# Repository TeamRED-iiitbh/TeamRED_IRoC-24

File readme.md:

View this project on [CADLAB.io](https://cadlab.io/project/27908). 

# TeamRED_IRoC-24

```bash
git clone https://github.com/TeamRED-iiitbh/TeamRED_IRoC-24.git
git submodule update --init
```

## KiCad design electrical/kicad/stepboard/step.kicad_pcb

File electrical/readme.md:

# Hardware

## Fritzing Circuit
The Fritzing circuit `electrocal\fritzing` includes various components for prototyping and visualization, such as temperature and humidity sensors, current sensors, and IMUs, all interconnected with the Arduino Giga board.

1. Adafruit AHT20 Temperature and Humidity Sensor
2. Adafruit INA219 Current Sensor FeatherWing
3. Adafruit INA219
4. Adafruit LSM6DS33 6-DoF Accel + Gyro IMU
5. Arduino-GIGA-R1-WIFI
6. AS5600 module
7. BMI160 breakout
8. Raspberry-Pi5
9. Seeed Wio E5
10. TMC2209 Bigtree

## Ki-Cad Projects

### GIGA Board - giga.kicad_pro

- DC Motor & 2-CH Encoder - Signal Pins
    DCx_PWM, DCx_
-  TMC2209 MakerBase

- AS5600 Module

### Power Board - pdb.kicad_pro

# Firware

### Stepper Motor Control with AS5600 Encoder

system that continuously moves the motor while displaying the encoder count. The setup uses an Arduino board with the AccelStepper library for motor control and interrupt-driven encoder reading for accurate feedback
- AccelStepper.h
- AS5600.h

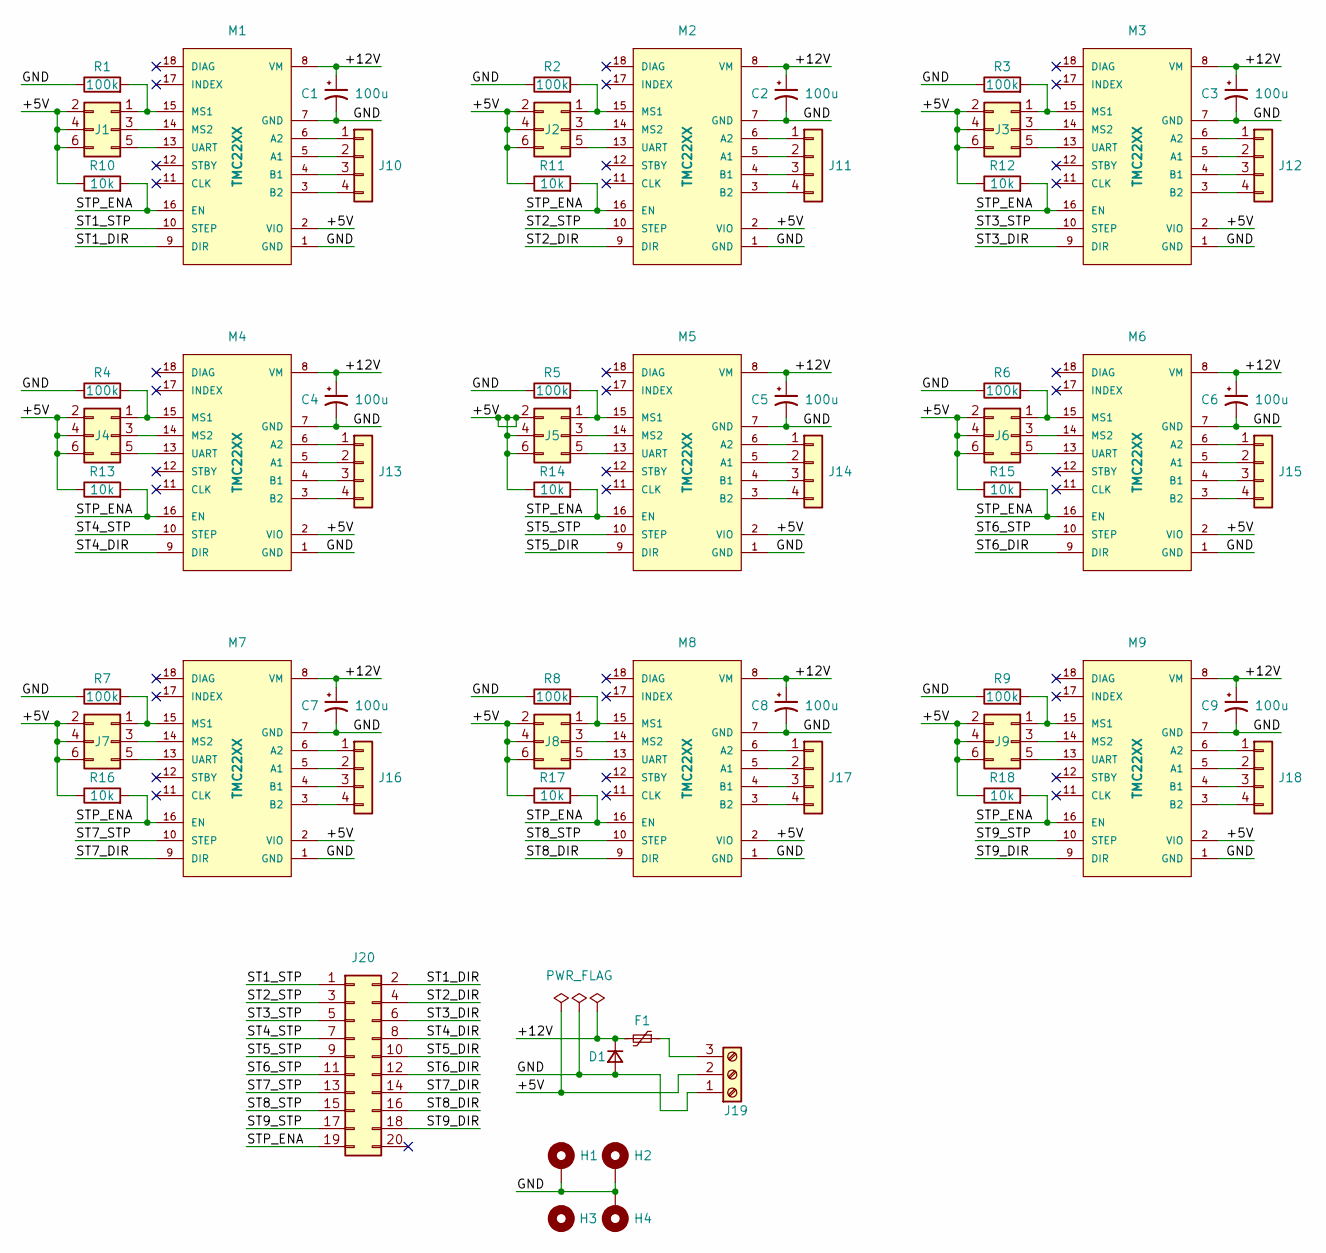
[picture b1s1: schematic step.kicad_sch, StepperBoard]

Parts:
C1, C2, C3, C4, C5, C6, C7, C8, C9: 100u; CP_Radial_D8.0mm_P2.50mm
D1: D_Small; D_DO-35_SOD27_P7.62mm_Horizontal
F1: Polyfuse_Small; Fuse_Tyco_RGEF1400
H1, H2, H4: MountingHole_Pad; MountingHole_3.2mm_M3_Pad_Via
H3: MountingHole; MountingHole_3.2mm_M3
J1, J2, J3, J4, J5, J6, J7, J8, J9: Conn_02x03_Odd_Even; PinHeader_2x03_P2.54mm_Vertical
J10, J11, J12, J13, J14, J15, J16, J17, J18: Conn_01x04; JST_XH_1x04_P2.54mm_Vertical
J19: Screw_Terminal_01x03; PhoenixContact_MSTBA_2,5_3-G-5,08_1x03_P5.08mm_Horizontal
J20: Conn_02x10_Odd_Even; PinHeader_2x10_P2.54mm_Vertical
M1, M2, M3, M4, M5, M6, M7, M8, M9: TMC22XX; MKS_TMC22XX
R1, R2, R3, R4, R5, R6, R7, R8, R9: 100k; R_Axial_DIN0204_L3.6mm_D1.6mm_P5.08mm_Horizontal
R10, R11, R12, R13, R14, R15, R16, R17, R18: 10k; R_Axial_DIN0204_L3.6mm_D1.6mm_P5.08mm_Horizontal

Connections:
/+5V: J1.2, J1.4, J1.6, J2.2, J2.4, J2.6, J3.2, J3.4, J3.6, J4.2, J4.4, J4.6, J5.2, J5.4, J5.6, J6.2, J6.4, J6.6, J7.2, J7.4, J7.6, J8.2, J8.4, J8.6, J9.2, J9.4, J9.6, J19.2, M1.2 (VIO), M2.2 (VIO), M3.2 (VIO), M4.2 (VIO), M5.2 (VIO), M6.2 (VIO), M7.2 (VIO), M8.2 (VIO), M9.2 (VIO), R10.1, R11.1, R12.1, R13.1, R14.1, R15.1, R16.1, R17.1, R18.1
/+12V: C1.1, C2.1, C3.1, C4.1, C5.1, C6.1, C7.1, C8.1, C9.1, D1.1 (K), F1.2, M1.8 (VM), M2.8 (VM), M3.8 (VM), M4.8 (VM), M5.8 (VM), M6.8 (VM), M7.8 (VM), M8.8 (VM), M9.8 (VM)
/GND: C1.2, C2.2, C3.2, C4.2, C5.2, C6.2, C7.2, C8.2, C9.2, D1.2 (A), H1.1, H2.1, H4.1, J19.1, M1.1 (GND), M1.7 (GND), M2.1 (GND), M2.7 (GND), M3.1 (GND), M3.7 (GND), M4.1 (GND), M4.7 (GND), M5.1 (GND), M5.7 (GND), M6.1 (GND), M6.7 (GND), M7.1 (GND), M7.7 (GND), M8.1 (GND), M8.7 (GND), M9.1 (GND), M9.7 (GND), R1.1, R2.1, R3.1, R4.1, R5.1, R6.1, R7.1, R8.1, R9.1
/ST1_DIR: J20.2, M1.9 (DIR)
/ST1_STP: J20.1, M1.10 (STEP)
/ST2_DIR: J20.4, M2.9 (DIR)
/ST2_STP: J20.3, M2.10 (STEP)
/ST3_DIR: J20.6, M3.9 (DIR)
/ST3_STP: J20.5, M3.10 (STEP)
/ST4_DIR: J20.8, M4.9 (DIR)
/ST4_STP: J20.7, M4.10 (STEP)
/ST5_DIR: J20.10, M5.9 (DIR)
/ST5_STP: J20.9, M5.10 (STEP)
/ST6_DIR: J20.12, M6.9 (DIR)
/ST6_STP: J20.11, M6.10 (STEP)
/ST7_DIR: J20.14, M7.9 (DIR)
/ST7_STP: J20.13, M7.10 (STEP)
/ST8_DIR: J20.16, M8.9 (DIR)
/ST8_STP: J20.15, M8.10 (STEP)
/ST9_DIR: J20.18, M9.9 (DIR)
/ST9_STP: J20.17, M9.10 (STEP)
/STP_ENA: J20.19, M1.16 (EN), M2.16 (EN), M3.16 (EN), M4.16 (EN), M5.16 (EN), M6.16 (EN), M7.16 (EN), M8.16 (EN), M9.16 (EN), R10.2, R11.2, R12.2, R13.2, R14.2, R15.2, R16.2, R17.2, R18.2
unnamed: J1.1, M1.15 (MS1), R1.2
unnamed: J1.3, M1.14 (MS2)
unnamed: J1.5, M1.13 (UART)
unnamed: J2.1, M2.15 (MS1), R2.2
unnamed: J2.3, M2.14 (MS2)
unnamed: J2.5, M2.13 (UART)
unnamed: J3.1, M3.15 (MS1), R3.2
unnamed: J3.3, M3.14 (MS2)
unnamed: J3.5, M3.13 (UART)
unnamed: J4.1, M4.15 (MS1), R4.2
unnamed: J4.3, M4.14 (MS2)
unnamed: J4.5, M4.13 (UART)
unnamed: J5.1, M5.15 (MS1), R5.2
unnamed: J5.3, M5.14 (MS2)
unnamed: J5.5, M5.13 (UART)
unnamed: J6.1, M6.15 (MS1), R6.2
unnamed: J6.3, M6.14 (MS2)
unnamed: J6.5, M6.13 (UART)
unnamed: J7.1, M7.15 (MS1), R7.2
unnamed: J7.3, M7.14 (MS2)
unnamed: J7.5, M7.13 (UART)
unnamed: J8.1, M8.15 (MS1), R8.2
unnamed: J8.3, M8.14 (MS2)
unnamed: J8.5, M8.13 (UART)
unnamed: J9.1, M9.15 (MS1), R9.2
unnamed: J9.3, M9.14 (MS2)
unnamed: J9.5, M9.13 (UART)
unnamed: J10.1, M1.6 (A2)
unnamed: J10.2, M1.5 (A1)
unnamed: J10.3, M1.4 (B1)
unnamed: J10.4, M1.3 (B2)
unnamed: J11.1, M2.6 (A2)
unnamed: J11.2, M2.5 (A1)
unnamed: J11.3, M2.4 (B1)
unnamed: J11.4, M2.3 (B2)
unnamed: J12.1, M3.6 (A2)
unnamed: J12.2, M3.5 (A1)
unnamed: J12.3, M3.4 (B1)
unnamed: J12.4, M3.3 (B2)
unnamed: J13.1, M4.6 (A2)
unnamed: J13.2, M4.5 (A1)
unnamed: J13.3, M4.4 (B1)
unnamed: J13.4, M4.3 (B2)
unnamed: J14.1, M5.6 (A2)
unnamed: J14.2, M5.5 (A1)
unnamed: J14.3, M5.4 (B1)
unnamed: J14.4, M5.3 (B2)
unnamed: J15.1, M6.6 (A2)
unnamed: J15.2, M6.5 (A1)
unnamed: J15.3, M6.4 (B1)
unnamed: J15.4, M6.3 (B2)
unnamed: J16.1, M7.6 (A2)
unnamed: J16.2, M7.5 (A1)
unnamed: J16.3, M7.4 (B1)
unnamed: J16.4, M7.3 (B2)
unnamed: J17.1, M8.6 (A2)
unnamed: J17.2, M8.5 (A1)
unnamed: J17.3, M8.4 (B1)
unnamed: J17.4, M8.3 (B2)
unnamed: J18.1, M9.6 (A2)
unnamed: J18.2, M9.5 (A1)
unnamed: J18.3, M9.4 (B1)
unnamed: J18.4, M9.3 (B2)
unnamed: F1.1, J19.3

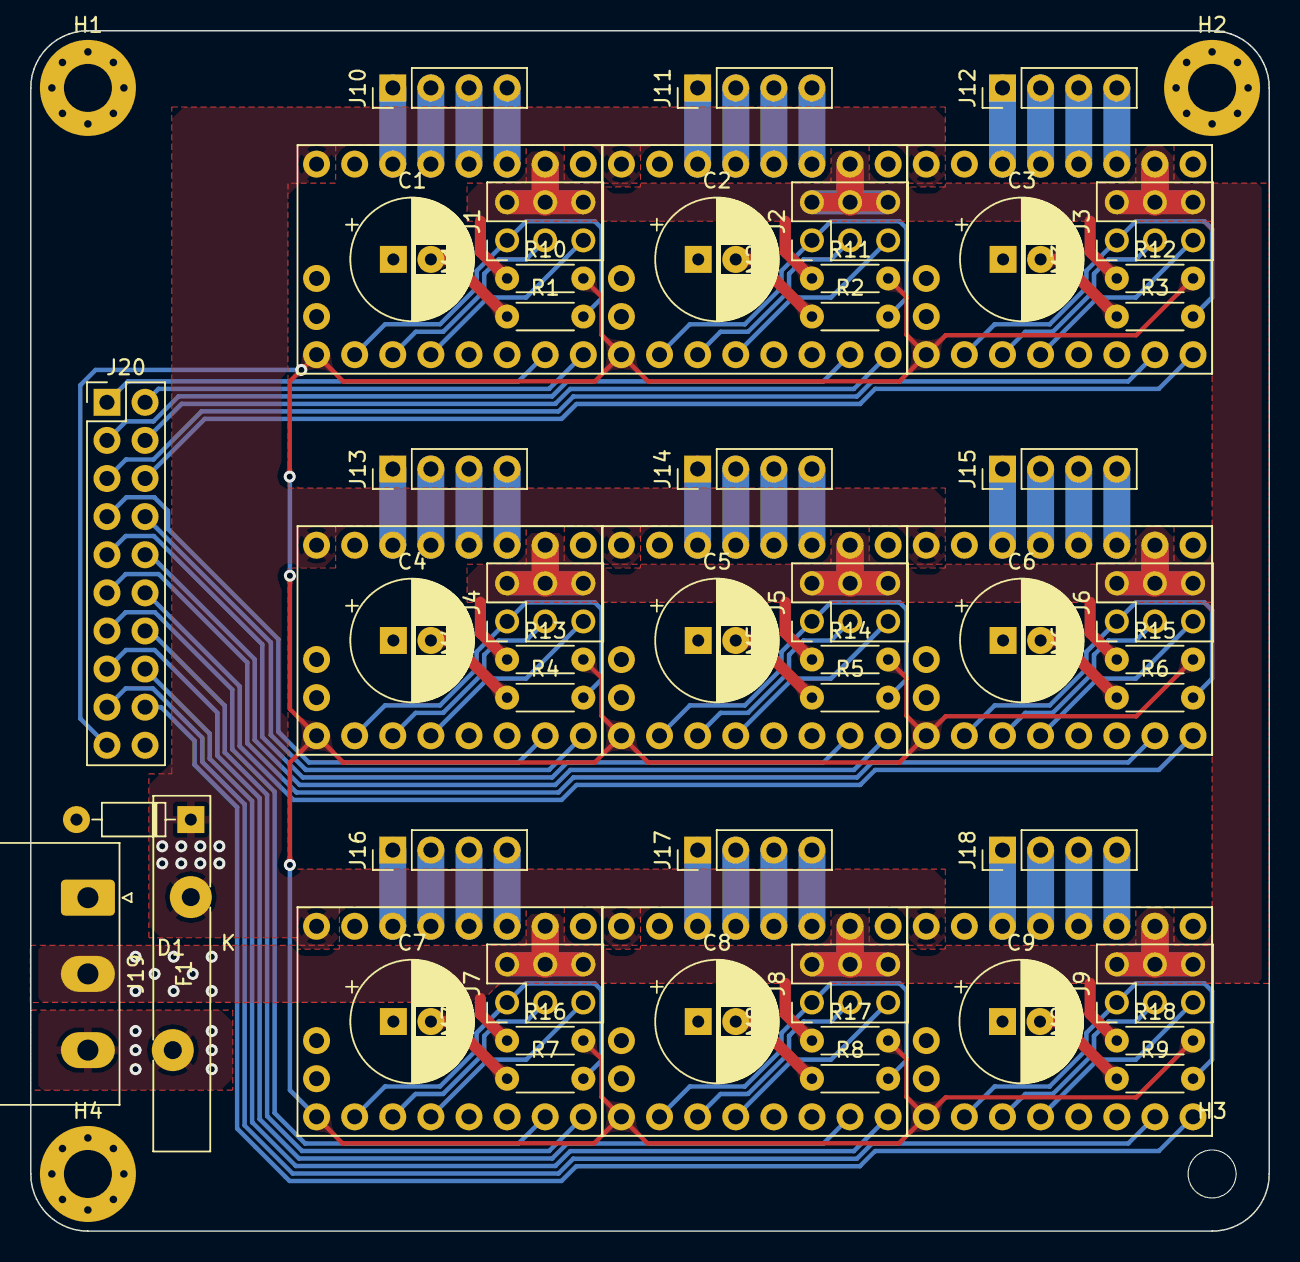
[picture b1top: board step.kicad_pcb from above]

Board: 2 copper layers, 82.6 x 80.0 mm, 62 parts (0 on the bottom side), 86 nets.

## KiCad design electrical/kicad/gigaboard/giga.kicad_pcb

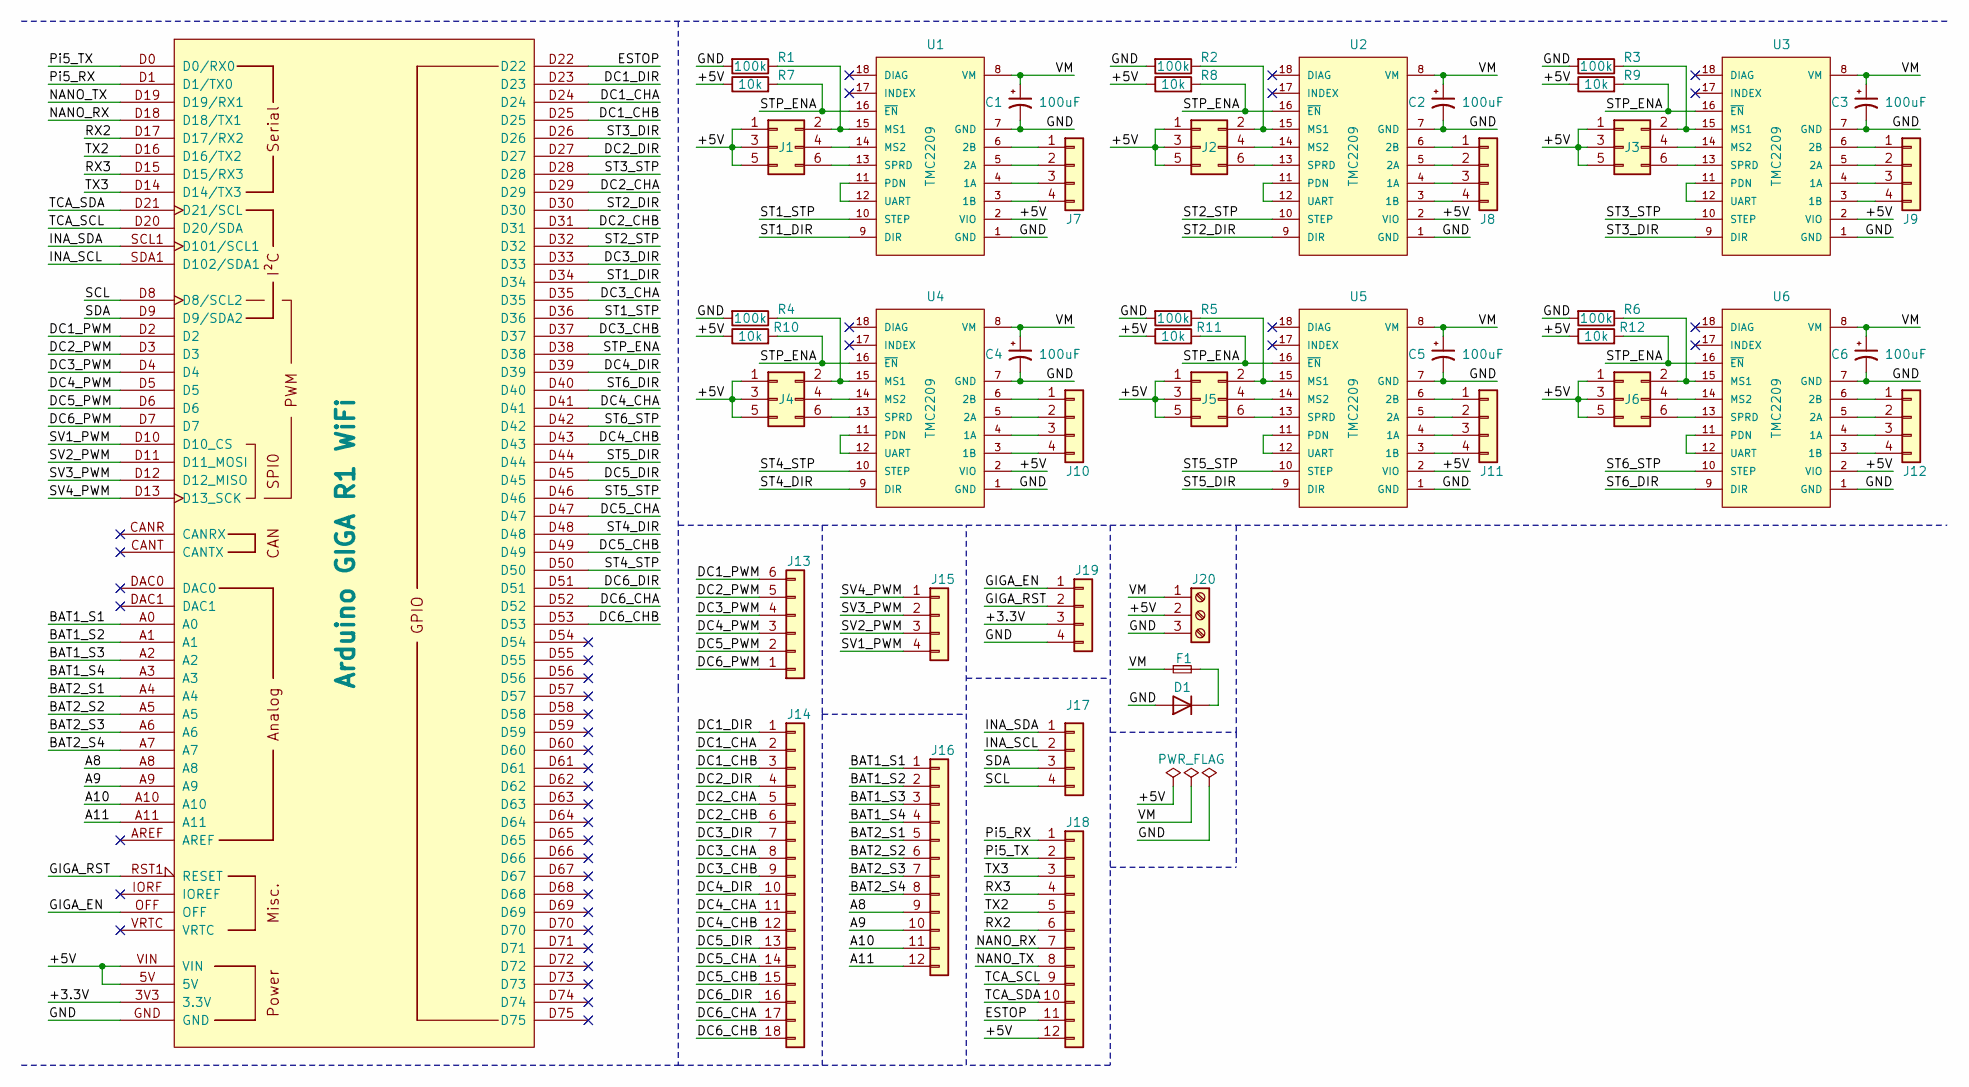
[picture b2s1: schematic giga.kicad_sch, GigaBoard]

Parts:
A1: Arduino GIGA R1 WiFi; Arduino_Giga-R1
C1, C2, C3, C4, C5, C6: 100uF; CP_Elec_6.3x7.7
D1: D; D_DO-35_SOD27_P7.62mm_Horizontal
F1: F_Small; Fuseholder_Blade_Mini_Keystone_3568
J1: Conn_02x03_Counter_Clockwise; PinHeader_2x03_P2.54mm_Vertical
J2, J3, J4, J5, J6: Conn_02x04_Counter_Clockwise; PinHeader_2x03_P2.54mm_Vertical
J7, J8, J9, J10, J11, J12, J15, J17, J19: Conn_01x04; PinHeader_1x04_P2.54mm_Vertical
J13: Conn_01x06; PinHeader_1x06_P2.54mm_Vertical
J14: Conn_01x18; PinHeader_1x18_P2.54mm_Vertical
J16, J18: Conn_01x12; PinHeader_1x12_P2.54mm_Vertical
J20: Screw_Terminal_01x03; PhoenixContact_MSTBA_2,5_3-G-5,08_1x03_P5.08mm_Horizontal
R1, R2, R3, R4, R5, R6: 100k; R_1206_3216Metric_Pad1.30x1.75mm_HandSolder
R7, R8, R9, R10, R11, R12: 10k; R_1206_3216Metric_Pad1.30x1.75mm_HandSolder
U1, U2, U3, U4, U5, U6: TMC2209; MKS_TMC2209

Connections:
/+3.3V: A1.3V3 (3.3V), J19.3
/+5V: A1.5V, A1.VIN, J1.1, J1.3, J1.5, J2.1, J2.3, J2.5, J3.1, J3.3, J3.5, J4.1, J4.3, J4.5, J5.1, J5.3, J5.5, J6.1, J6.3, J6.5, J18.12, J20.2, R7.1, R8.1, R9.1, R10.1, R11.1, R12.1, U1.2 (VIO), U2.2 (VIO), U3.2 (VIO), U4.2 (VIO), U5.2 (VIO), U6.2 (VIO)
/A8: A1.A8, J16.9
/A9: A1.A9, J16.10
/A10: A1.A10, J16.11
/A11: A1.A11, J16.12
/BAT1_S1: A1.A0, J16.1
/BAT1_S2: A1.A1, J16.2
/BAT1_S3: A1.A2, J16.3
/BAT1_S4: A1.A3, J16.4
/BAT2_S1: A1.A4, J16.5
/BAT2_S2: A1.A5, J16.6
/BAT2_S3: A1.A6, J16.7
/BAT2_S4: A1.A7, J16.8
/DC1_CHA: A1.D24, J14.2
/DC1_CHB: A1.D25, J14.3
/DC1_DIR: A1.D23, J14.1
/DC1_PWM: A1.D2, J13.6
/DC2_CHA: A1.D29, J14.5
/DC2_CHB: A1.D31, J14.6
/DC2_DIR: A1.D27, J14.4
/DC2_PWM: A1.D3, J13.5
/DC3_CHA: A1.D35, J14.8
/DC3_CHB: A1.D37, J14.9
/DC3_DIR: A1.D33, J14.7
/DC3_PWM: A1.D4, J13.4
/DC4_CHA: A1.D41, J14.11
/DC4_CHB: A1.D43, J14.12
/DC4_DIR: A1.D39, J14.10
/DC4_PWM: A1.D5, J13.3
/DC5_CHA: A1.D47, J14.14
/DC5_CHB: A1.D49, J14.15
/DC5_DIR: A1.D45, J14.13
/DC5_PWM: A1.D6, J13.2
/DC6_CHA: A1.D52, J14.17
/DC6_CHB: A1.D53, J14.18
/DC6_DIR: A1.D51, J14.16
/DC6_PWM: A1.D7, J13.1
/ESTOP: A1.D22, J18.11
/GIGA_EN: A1.OFF, J19.1
/GIGA_RST: A1.RST1 (RESET), J19.2
/GND: A1.GND, C1.2, C2.2, C3.2, C4.2, C5.2, C6.2, D1.2 (A), J19.4, J20.3, R1.2, R2.2, R3.2, R4.2, R5.2, R6.2, U1.1 (GND), U1.7 (GND), U2.1 (GND), U2.7 (GND), U3.1 (GND), U3.7 (GND), U4.1 (GND), U4.7 (GND), U5.1 (GND), U5.7 (GND), U6.1 (GND), U6.7 (GND)
/INA_SCL: A1.SDA1 (D102/SDA1), J17.2
/INA_SDA: A1.SCL1 (D101/SCL1), J17.1
/NANO_RX: A1.D18 (D18/TX1), J18.7
/NANO_TX: A1.D19 (D19/RX1), J18.8
/Pi5_RX: A1.D1 (D1/TX0), J18.1
/Pi5_TX: A1.D0 (D0/RX0), J18.2
/RX2: A1.D17 (D17/RX2), J18.6
/RX3: A1.D15 (D15/RX3), J18.4
/SCL: A1.D8 (D8/SCL2), J17.4
/SDA: A1.D9 (D9/SDA2), J17.3
/ST1_DIR: A1.D34, U1.9 (DIR)
/ST1_STP: A1.D36, U1.10 (STEP)
/ST2_DIR: A1.D30, U2.9 (DIR)
/ST2_STP: A1.D32, U2.10 (STEP)
/ST3_DIR: A1.D26, U3.9 (DIR)
/ST3_STP: A1.D28, U3.10 (STEP)
/ST4_DIR: A1.D48, U4.9 (DIR)
/ST4_STP: A1.D50, U4.10 (STEP)
/ST5_DIR: A1.D44, U5.9 (DIR)
/ST5_STP: A1.D46, U5.10 (STEP)
/ST6_DIR: A1.D40, U6.9 (DIR)
/ST6_STP: A1.D42, U6.10 (STEP)
/STP_ENA: A1.D38, R7.2, R8.2, R9.2, R10.2, R11.2, R12.2, U1.16 (~EN), U2.16 (~EN), U3.16 (~EN), U4.16 (~EN), U5.16 (~EN), U6.16 (~EN)
/SV1_PWM: A1.D10 (D10_CS), J15.4
/SV2_PWM: A1.D11 (D11_MOSI), J15.3
/SV3_PWM: A1.D12 (D12_MISO), J15.2
/SV4_PWM: A1.D13 (D13_SCK), J15.1
/TCA_SCL: A1.D20 (D20/SDA), J18.9
/TCA_SDA: A1.D21 (D21/SCL), J18.10
/TX2: A1.D16 (D16/TX2), J18.5
/TX3: A1.D14 (D14/TX3), J18.3
/VM: C1.1, C2.1, C3.1, C4.1, C5.1, C6.1, F1.1, J20.1, U1.8 (VM), U2.8 (VM), U3.8 (VM), U4.8 (VM), U5.8 (VM), U6.8 (VM)
unnamed: D1.1 (K), F1.2
unnamed: J1.2, R1.1, U1.15 (MS1)
unnamed: J1.4, U1.14 (MS2)
unnamed: J1.6, U1.13 (SPRD)
unnamed: J2.2, R2.1, U2.15 (MS1)
unnamed: J2.4, U2.14 (MS2)
unnamed: J2.6, U2.13 (SPRD)
unnamed: J3.2, R3.1, U3.15 (MS1)
unnamed: J3.4, U3.14 (MS2)
unnamed: J3.6, U3.13 (SPRD)
unnamed: J4.2, R4.1, U4.15 (MS1)
unnamed: J4.4, U4.14 (MS2)
unnamed: J4.6, U4.13 (SPRD)
unnamed: J5.2, R5.1, U5.15 (MS1)
unnamed: J5.4, U5.14 (MS2)
unnamed: J5.6, U5.13 (SPRD)
unnamed: J6.2, R6.1, U6.15 (MS1)
unnamed: J6.4, U6.14 (MS2)
unnamed: J6.6, U6.13 (SPRD)
unnamed: J7.1, U1.6 (2B)
unnamed: J7.2, U1.5 (2A)
unnamed: J7.3, U1.4 (1A)
unnamed: J7.4, U1.3 (1B)
unnamed: J8.1, U2.6 (2B)
unnamed: J8.2, U2.5 (2A)
unnamed: J8.3, U2.4 (1A)
unnamed: J8.4, U2.3 (1B)
unnamed: J9.1, U3.6 (2B)
unnamed: J9.2, U3.5 (2A)
unnamed: J9.3, U3.4 (1A)
unnamed: J9.4, U3.3 (1B)
unnamed: J10.1, U4.6 (2B)
unnamed: J10.2, U4.5 (2A)
unnamed: J10.3, U4.4 (1A)
unnamed: J10.4, U4.3 (1B)
unnamed: J11.1, U5.6 (2B)
unnamed: J11.2, U5.5 (2A)
unnamed: J11.3, U5.4 (1A)
unnamed: J11.4, U5.3 (1B)
unnamed: J12.1, U6.6 (2B)
unnamed: J12.2, U6.5 (2A)
unnamed: J12.3, U6.4 (1A)
unnamed: J12.4, U6.3 (1B)
unnamed: U1.11 (PDN), U1.12 (UART)
unnamed: U2.11 (PDN), U2.12 (UART)
unnamed: U3.11 (PDN), U3.12 (UART)
unnamed: U4.11 (PDN), U4.12 (UART)
unnamed: U5.11 (PDN), U5.12 (UART)
unnamed: U6.11 (PDN), U6.12 (UART)

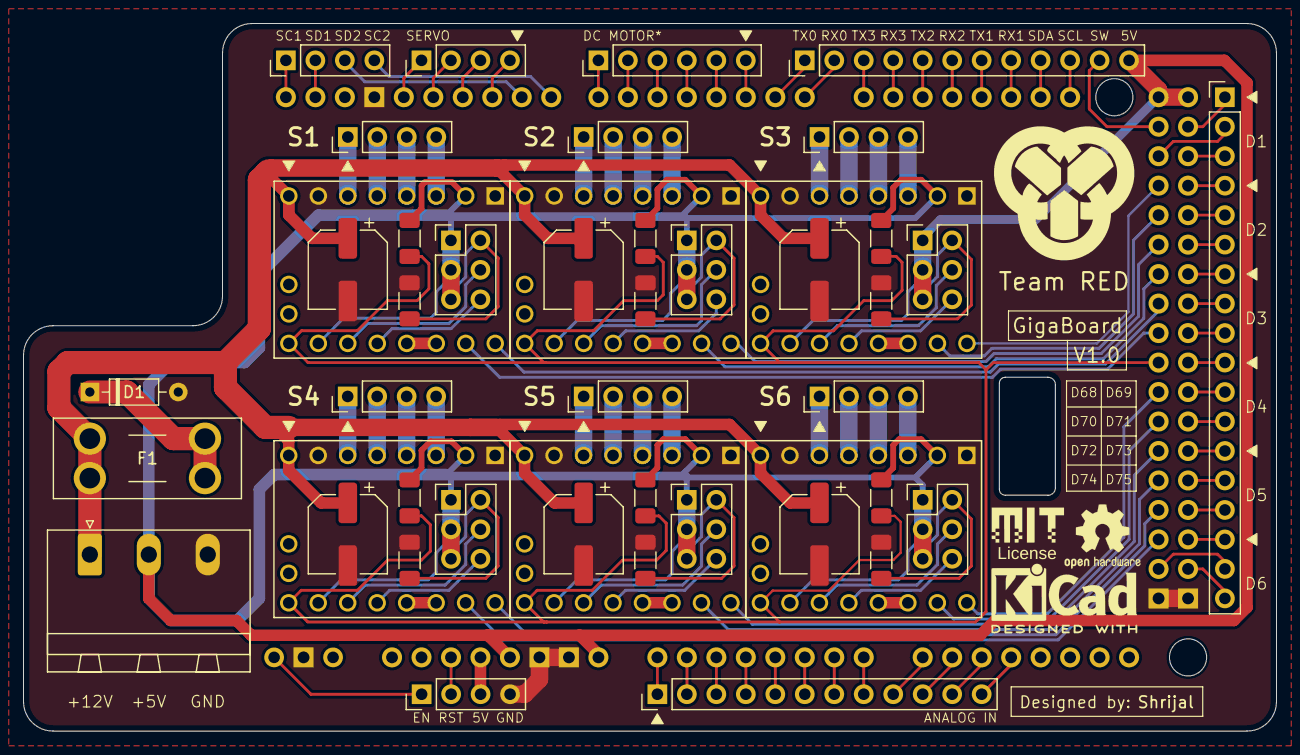
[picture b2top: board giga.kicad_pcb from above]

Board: 2 copper layers, 108.0 x 61.0 mm, 47 parts (0 on the bottom side), 123 nets.

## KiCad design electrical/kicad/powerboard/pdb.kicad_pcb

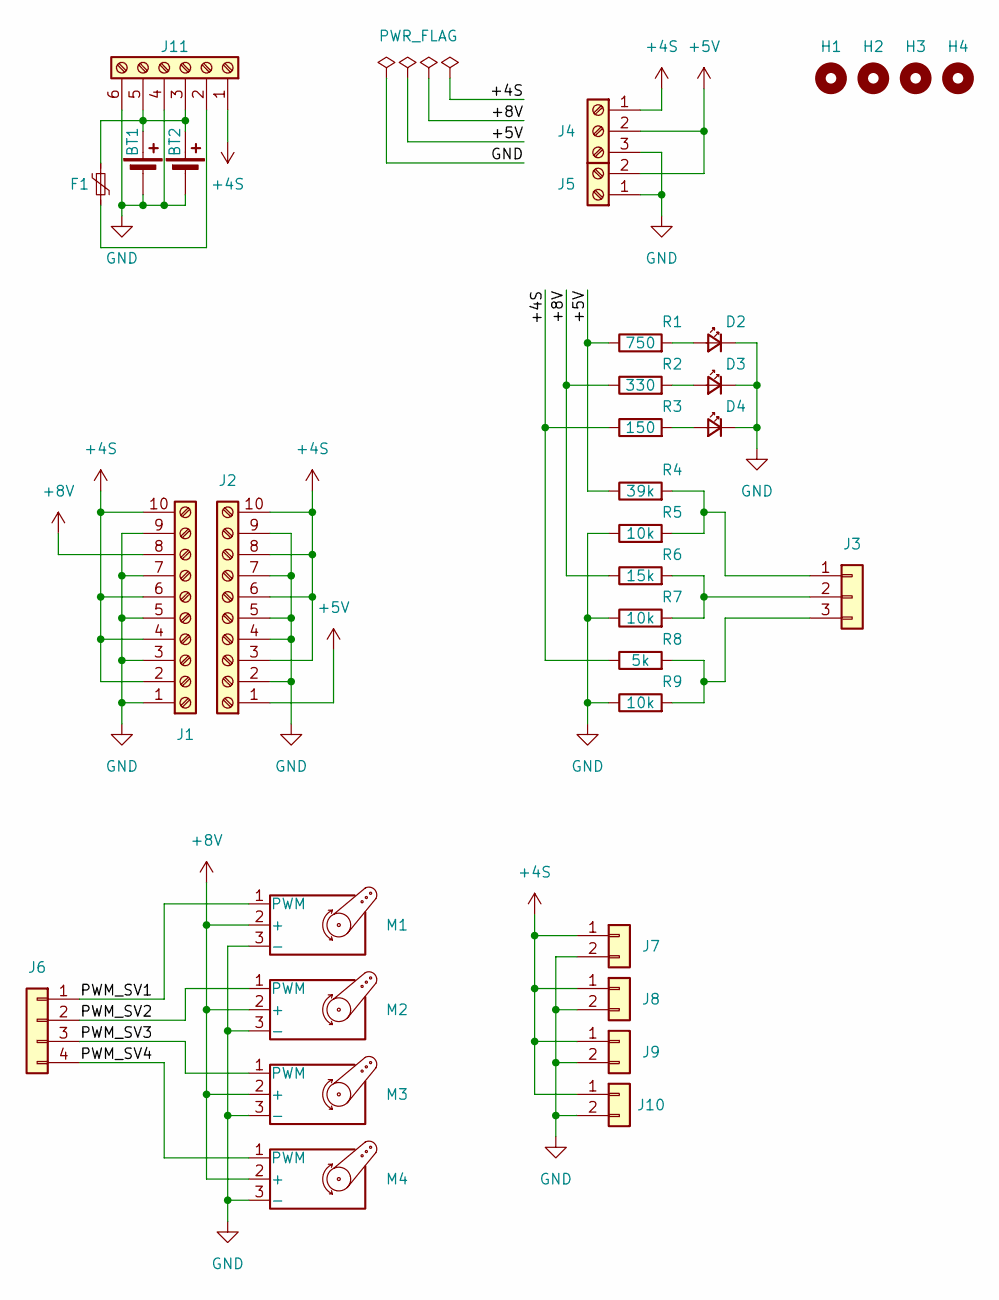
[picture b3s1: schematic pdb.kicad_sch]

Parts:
BT1, BT2: Battery_Cell; PhoenixContact_MSTBA_2,5_2-G-5,08_1x02_P5.08mm_Horizontal
D2, D3, D4: LED_Small; LED_D3.0mm_Clear
F1: Polyfuse_Small; Fuse_Tyco_RGEF1400
H1, H2, H3, H4: MountingHole; MountingHole_3.2mm_M3
J1, J2: Screw_Terminal_01x10; PhoenixContact_MSTBA_2,5_10-G-5,08_1x10_P5.08mm_Horizontal
J3: Conn_01x03; JST_XH_1x03_P2.54mm_Vertical
J4: Screw_Terminal_01x03; PhoenixContact_MSTBA_2,5_3-G-5,08_1x03_P5.08mm_Horizontal
J5: Screw_Terminal_01x02; PhoenixContact_MSTBA_2,5_2-G-5,08_1x02_P5.08mm_Horizontal
J6: Conn_01x04; JST_XH_1x04_P2.54mm_Vertical
J7, J8, J9, J10: Conn_01x02; PinHeader_1x02_P2.54mm_Vertical
J11: Screw_Terminal_01x06; PhoenixContact_MSTBA_2,5_6-G-5,08_1x06_P5.08mm_Horizontal
M1, M2, M3, M4: Motor_Servo; PinHeader_1x03_P2.54mm_Vertical
R1: 750; R_Axial_DIN0207_L6.3mm_D2.5mm_P7.62mm_Horizontal
R2: 330; R_Axial_DIN0207_L6.3mm_D2.5mm_P7.62mm_Horizontal
R3: 150; R_Axial_DIN0207_L6.3mm_D2.5mm_P7.62mm_Horizontal
R4: 39k; R_Axial_DIN0207_L6.3mm_D2.5mm_P7.62mm_Horizontal
R5, R7, R9: 10k; R_Axial_DIN0207_L6.3mm_D2.5mm_P7.62mm_Horizontal
R6: 15k; R_Axial_DIN0207_L6.3mm_D2.5mm_P7.62mm_Horizontal
R8: 5k; R_Axial_DIN0207_L6.3mm_D2.5mm_P7.62mm_Horizontal

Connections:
+4S: J1.2, J1.4, J1.6, J1.10, J2.3, J2.6, J2.8, J2.10, J4.1, J7.1, J8.1, J9.1, J10.1, J11.1, R3.1, R8.1
+5V: J2.1, J4.2, J5.2, R1.1, R4.1
+8V: J1.8, M1.2 (+), M2.2 (+), M3.2 (+), M4.2 (+), R2.1, R6.1
/PWM_SV1: J6.1, M1.1 (PWM)
/PWM_SV2: J6.2, M2.1 (PWM)
/PWM_SV3: J6.3, M3.1 (PWM)
/PWM_SV4: J6.4, M4.1 (PWM)
GND: BT1.2 (-), BT2.2 (-), D2.1 (K), D3.1 (K), D4.1 (K), J1.1, J1.3, J1.5, J1.7, J1.9, J2.2, J2.4, J2.5, J2.7, J2.9, J4.3, J5.1, J7.2, J8.2, J9.2, J10.2, J11.4, J11.6, M1.3 (-), M2.3 (-), M3.3 (-), M4.3 (-), R5.1, R7.1, R9.1
unnamed: D2.2 (A), R1.2
unnamed: D3.2 (A), R2.2
unnamed: D4.2 (A), R3.2
unnamed: J3.1, R4.2, R5.2
unnamed: J3.2, R6.2, R7.2
unnamed: J3.3, R8.2, R9.2
unnamed: F1.2, J11.2
unnamed: BT1.1 (+), BT2.1 (+), F1.1, J11.3, J11.5

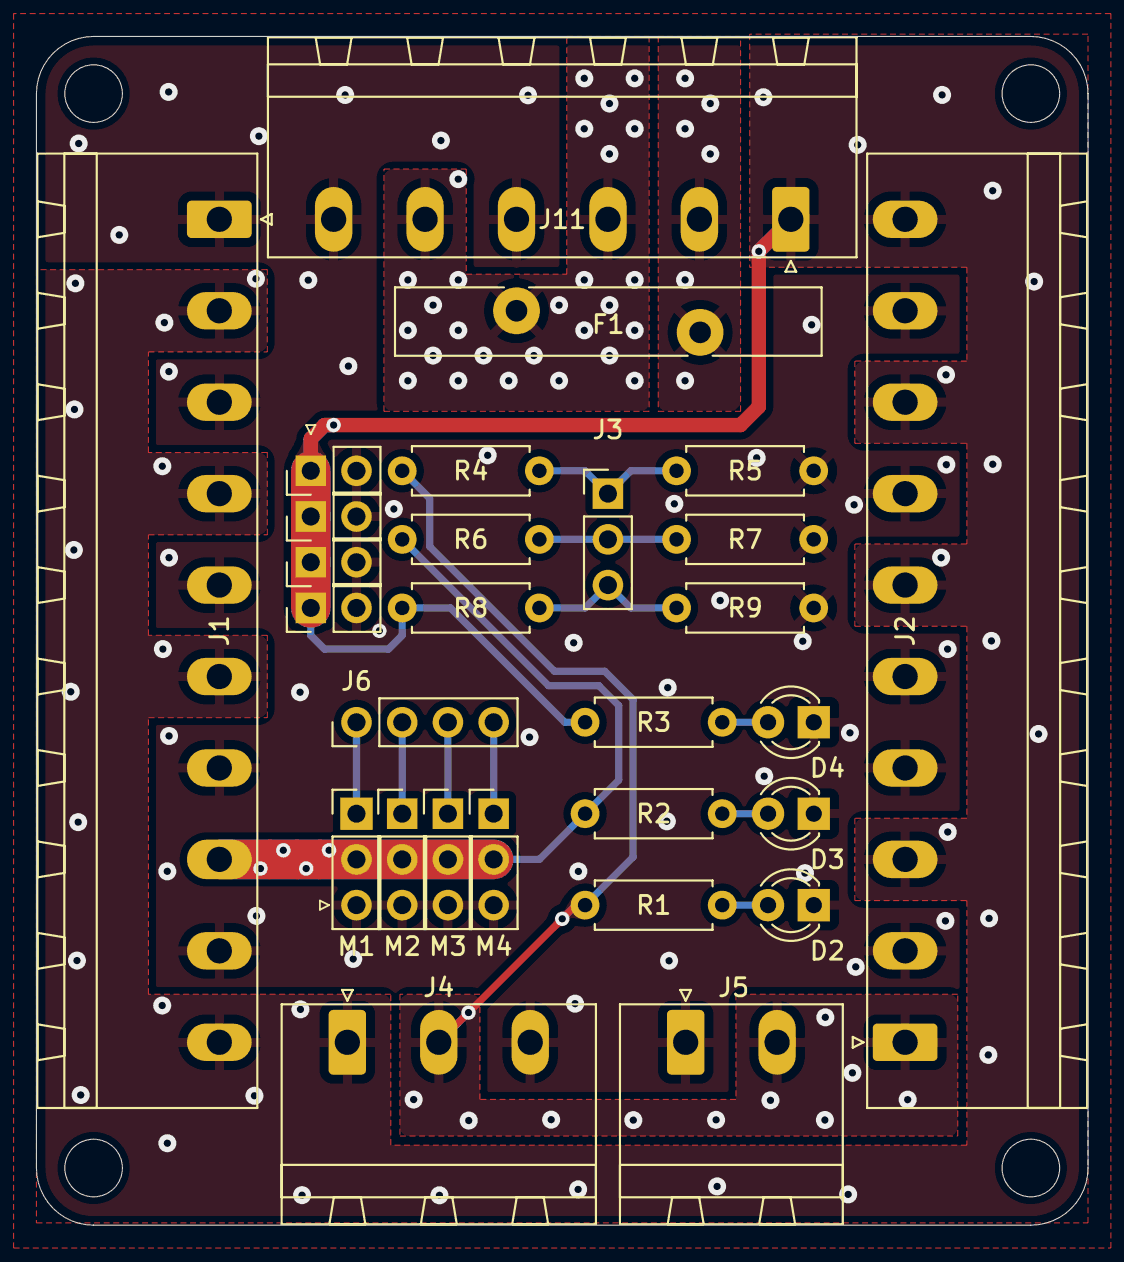
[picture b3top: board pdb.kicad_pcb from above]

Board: 2 copper layers, 58.4 x 66.0 mm, 32 parts (0 on the bottom side), 16 nets.

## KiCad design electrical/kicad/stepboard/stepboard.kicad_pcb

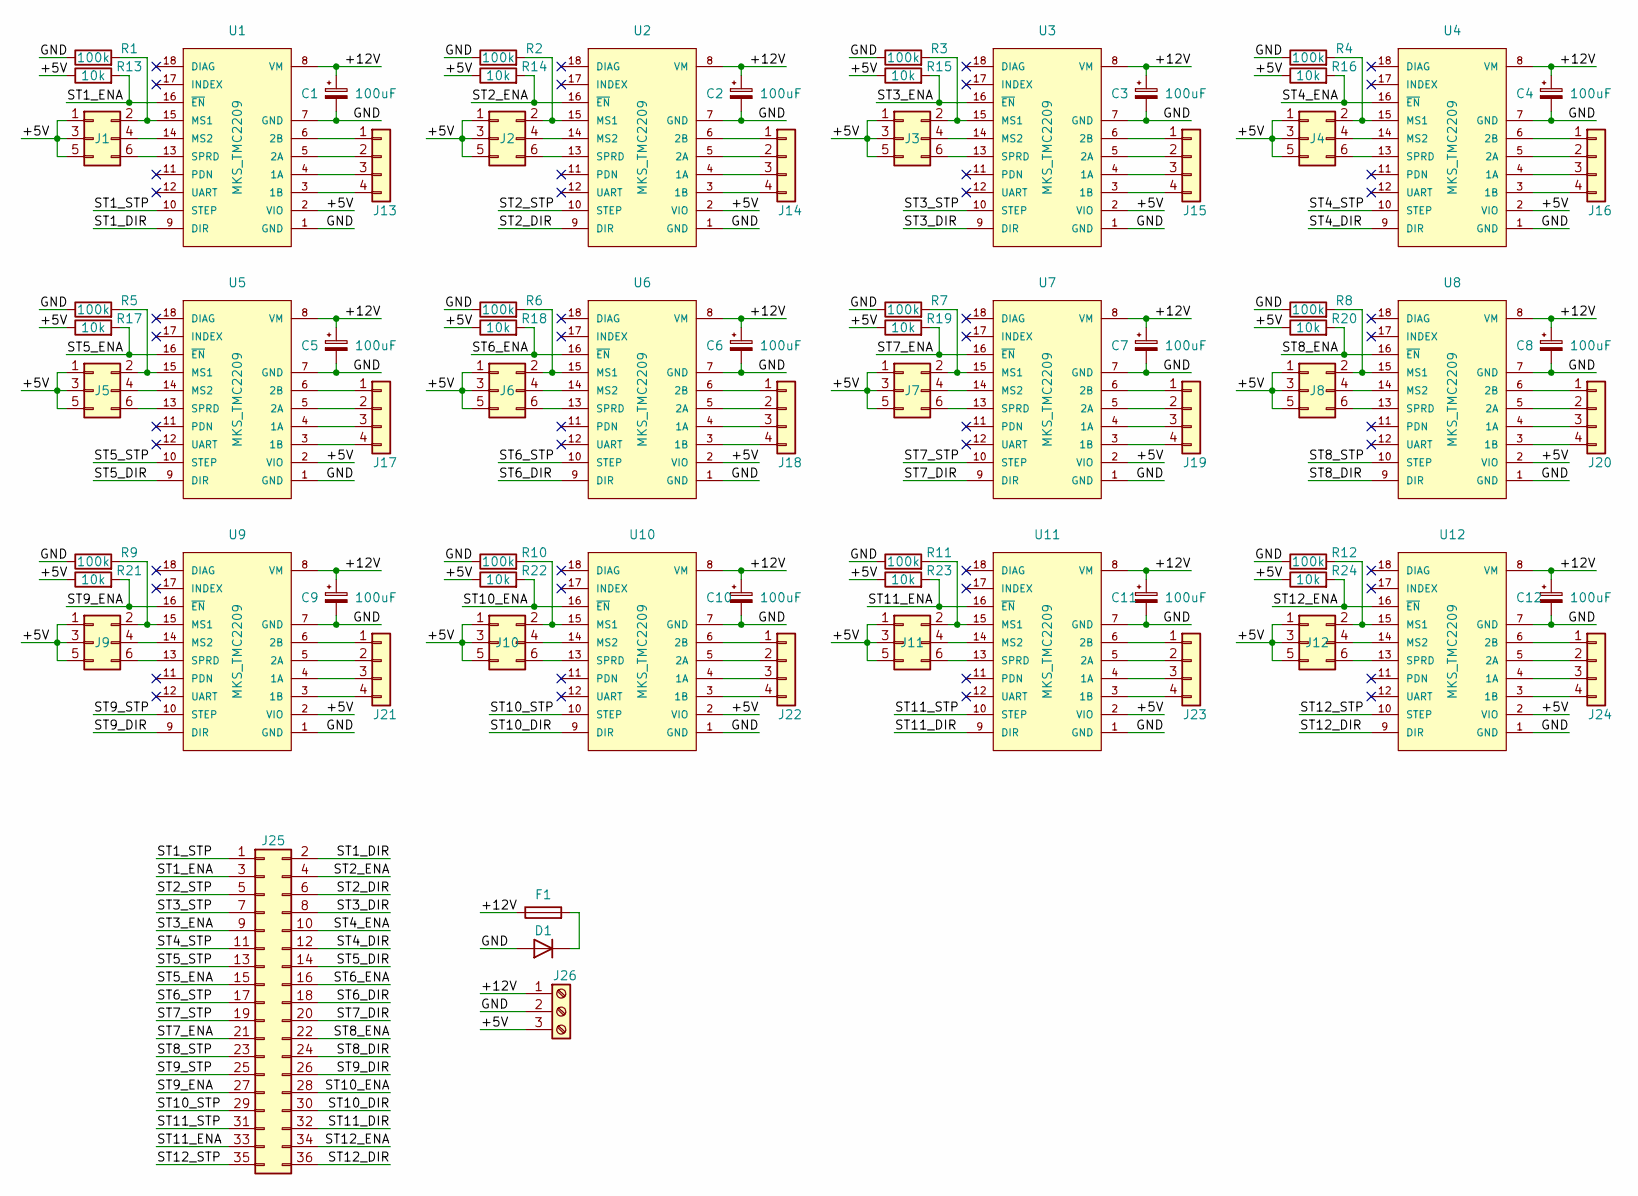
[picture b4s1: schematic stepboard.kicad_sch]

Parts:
C1, C2, C3, C4, C5, C6, C7, C8, C9, C10, C11, C12: 100uF; CP_Radial_D8.0mm_P3.50mm_H12.0mm_Horizontal
D1: D; D_DO-35_SOD27_P7.62mm_Horizontal
F1: Fuse; Fuse_Tyco-RUEF900
J1, J2, J3, J4, J5, J6, J7, J8, J9, J10, J11, J12: Conn_02x03_Odd_Even; PinHeader_2x03_P2.54mm_Vertical
J13, J14, J15, J16, J17, J18, J19, J20, J21, J22, J23, J24: Conn_01x04; PinHeader_1x04_P2.54mm_Vertical
J25: Conn_02x18_Odd_Even; PinHeader_2x18_P2.54mm_Vertical
J26: Screw_Terminal_01x03; PhoenixContact_MSTBA_2,5_3-G-5,08_1x03_P5.08mm_Horizontal
R1, R2, R3, R4, R5, R6, R7, R8, R9, R10, R11, R12: 100k; R_Axial_DIN0207_L6.3mm_D2.5mm_P7.62mm_Horizontal
R13, R14, R15, R16, R17, R18, R19, R20, R21, R22, R23, R24: 10k; R_Axial_DIN0207_L6.3mm_D2.5mm_P7.62mm_Horizontal
U1, U2, U3, U4, U5, U6, U7, U8, U9, U10, U11, U12: MKS_TMC2209

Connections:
/+5V: J1.1, J1.3, J1.5, J2.1, J2.3, J2.5, J3.1, J3.3, J3.5, J4.1, J4.3, J4.5, J5.1, J5.3, J5.5, J6.1, J6.3, J6.5, J7.1, J7.3, J7.5, J8.1, J8.3, J8.5, J9.1, J9.3, J9.5, J10.1, J10.3, J10.5, J11.1, J11.3, J11.5, J12.1, J12.3, J12.5, J26.3, R13.1, R14.1, R15.1, R16.1, R17.1, R18.1, R19.1, R20.1, R21.1, R22.1, R23.1, R24.1, U1.2 (VIO), U2.2 (VIO), U3.2 (VIO), U4.2 (VIO), U5.2 (VIO), U6.2 (VIO), U7.2 (VIO), U8.2 (VIO), U9.2 (VIO), U10.2 (VIO), U11.2 (VIO), U12.2 (VIO)
/+12V: C1.1, C2.1, C3.1, C4.1, C5.1, C6.1, C7.1, C8.1, C9.1, C10.1, C11.1, C12.1, F1.1, J26.1, U1.8 (VM), U2.8 (VM), U3.8 (VM), U4.8 (VM), U5.8 (VM), U6.8 (VM), U7.8 (VM), U8.8 (VM), U9.8 (VM), U10.8 (VM), U11.8 (VM), U12.8 (VM)
/GND: C1.2, C2.2, C3.2, C4.2, C5.2, C6.2, C7.2, C8.2, C9.2, C10.2, C11.2, C12.2, D1.2 (A), J26.2, R1.1, R2.1, R3.1, R4.1, R5.1, R6.1, R7.1, R8.1, R9.1, R10.1, R11.1, R12.1, U1.1 (GND), U1.7 (GND), U2.1 (GND), U2.7 (GND), U3.1 (GND), U3.7 (GND), U4.1 (GND), U4.7 (GND), U5.1 (GND), U5.7 (GND), U6.1 (GND), U6.7 (GND), U7.1 (GND), U7.7 (GND), U8.1 (GND), U8.7 (GND), U9.1 (GND), U9.7 (GND), U10.1 (GND), U10.7 (GND), U11.1 (GND), U11.7 (GND), U12.1 (GND), U12.7 (GND)
/ST1_DIR: J25.2, U1.9 (DIR)
/ST1_ENA: J25.3, R13.2, U1.16 (~EN)
/ST1_STP: J25.1, U1.10 (STEP)
/ST2_DIR: J25.6, U2.9 (DIR)
/ST2_ENA: J25.4, R14.2, U2.16 (~EN)
/ST2_STP: J25.5, U2.10 (STEP)
/ST3_DIR: J25.8, U3.9 (DIR)
/ST3_ENA: J25.9, R15.2, U3.16 (~EN)
/ST3_STP: J25.7, U3.10 (STEP)
/ST4_DIR: J25.12, U4.9 (DIR)
/ST4_ENA: J25.10, R16.2, U4.16 (~EN)
/ST4_STP: J25.11, U4.10 (STEP)
/ST5_DIR: J25.14, U5.9 (DIR)
/ST5_ENA: J25.15, R17.2, U5.16 (~EN)
/ST5_STP: J25.13, U5.10 (STEP)
/ST6_DIR: J25.18, U6.9 (DIR)
/ST6_ENA: J25.16, R18.2, U6.16 (~EN)
/ST6_STP: J25.17, U6.10 (STEP)
/ST7_DIR: J25.20, U7.9 (DIR)
/ST7_ENA: J25.21, R19.2, U7.16 (~EN)
/ST7_STP: J25.19, U7.10 (STEP)
/ST8_DIR: J25.24, U8.9 (DIR)
/ST8_ENA: J25.22, R20.2, U8.16 (~EN)
/ST8_STP: J25.23, U8.10 (STEP)
/ST9_DIR: J25.26, U9.9 (DIR)
/ST9_ENA: J25.27, R21.2, U9.16 (~EN)
/ST9_STP: J25.25, U9.10 (STEP)
/ST10_DIR: J25.30, U10.9 (DIR)
/ST10_ENA: J25.28, R22.2, U10.16 (~EN)
/ST10_STP: J25.29, U10.10 (STEP)
/ST11_DIR: J25.32, U11.9 (DIR)
/ST11_ENA: J25.33, R23.2, U11.16 (~EN)
/ST11_STP: J25.31, U11.10 (STEP)
/ST12_DIR: J25.36, U12.9 (DIR)
/ST12_ENA: J25.34, R24.2, U12.16 (~EN)
/ST12_STP: J25.35, U12.10 (STEP)
unnamed: D1.1 (K), F1.2
unnamed: J1.2, R1.2, U1.15 (MS1)
unnamed: J1.4, U1.14 (MS2)
unnamed: J1.6, U1.13 (SPRD)
unnamed: J2.2, R2.2, U2.15 (MS1)
unnamed: J2.4, U2.14 (MS2)
unnamed: J2.6, U2.13 (SPRD)
unnamed: J3.2, R3.2, U3.15 (MS1)
unnamed: J3.4, U3.14 (MS2)
unnamed: J3.6, U3.13 (SPRD)
unnamed: J4.2, R4.2, U4.15 (MS1)
unnamed: J4.4, U4.14 (MS2)
unnamed: J4.6, U4.13 (SPRD)
unnamed: J5.2, R5.2, U5.15 (MS1)
unnamed: J5.4, U5.14 (MS2)
unnamed: J5.6, U5.13 (SPRD)
unnamed: J6.2, R6.2, U6.15 (MS1)
unnamed: J6.4, U6.14 (MS2)
unnamed: J6.6, U6.13 (SPRD)
unnamed: J7.2, R7.2, U7.15 (MS1)
unnamed: J7.4, U7.14 (MS2)
unnamed: J7.6, U7.13 (SPRD)
unnamed: J8.2, R8.2, U8.15 (MS1)
unnamed: J8.4, U8.14 (MS2)
unnamed: J8.6, U8.13 (SPRD)
unnamed: J9.2, R9.2, U9.15 (MS1)
unnamed: J9.4, U9.14 (MS2)
unnamed: J9.6, U9.13 (SPRD)
unnamed: J10.2, R10.2, U10.15 (MS1)
unnamed: J10.4, U10.14 (MS2)
unnamed: J10.6, U10.13 (SPRD)
unnamed: J11.2, R11.2, U11.15 (MS1)
unnamed: J11.4, U11.14 (MS2)
unnamed: J11.6, U11.13 (SPRD)
unnamed: J12.2, R12.2, U12.15 (MS1)
unnamed: J12.4, U12.14 (MS2)
unnamed: J12.6, U12.13 (SPRD)
unnamed: J13.1, U1.6 (2B)
unnamed: J13.2, U1.5 (2A)
unnamed: J13.3, U1.4 (1A)
unnamed: J13.4, U1.3 (1B)
unnamed: J14.1, U2.6 (2B)
unnamed: J14.2, U2.5 (2A)
unnamed: J14.3, U2.4 (1A)
unnamed: J14.4, U2.3 (1B)
unnamed: J15.1, U3.6 (2B)
unnamed: J15.2, U3.5 (2A)
unnamed: J15.3, U3.4 (1A)
unnamed: J15.4, U3.3 (1B)
unnamed: J16.1, U4.6 (2B)
unnamed: J16.2, U4.5 (2A)
unnamed: J16.3, U4.4 (1A)
unnamed: J16.4, U4.3 (1B)
unnamed: J17.1, U5.6 (2B)
unnamed: J17.2, U5.5 (2A)
unnamed: J17.3, U5.4 (1A)
unnamed: J17.4, U5.3 (1B)
unnamed: J18.1, U6.6 (2B)
unnamed: J18.2, U6.5 (2A)
unnamed: J18.3, U6.4 (1A)
unnamed: J18.4, U6.3 (1B)
unnamed: J19.1, U7.6 (2B)
unnamed: J19.2, U7.5 (2A)
unnamed: J19.3, U7.4 (1A)
unnamed: J19.4, U7.3 (1B)
unnamed: J20.1, U8.6 (2B)
unnamed: J20.2, U8.5 (2A)
unnamed: J20.3, U8.4 (1A)
unnamed: J20.4, U8.3 (1B)
unnamed: J21.1, U9.6 (2B)
unnamed: J21.2, U9.5 (2A)
unnamed: J21.3, U9.4 (1A)
unnamed: J21.4, U9.3 (1B)
unnamed: J22.1, U10.6 (2B)
unnamed: J22.2, U10.5 (2A)
unnamed: J22.3, U10.4 (1A)
unnamed: J22.4, U10.3 (1B)
unnamed: J23.1, U11.6 (2B)
unnamed: J23.2, U11.5 (2A)
unnamed: J23.3, U11.4 (1A)
unnamed: J23.4, U11.3 (1B)
unnamed: J24.1, U12.6 (2B)
unnamed: J24.2, U12.5 (2A)
unnamed: J24.3, U12.4 (1A)
unnamed: J24.4, U12.3 (1B)

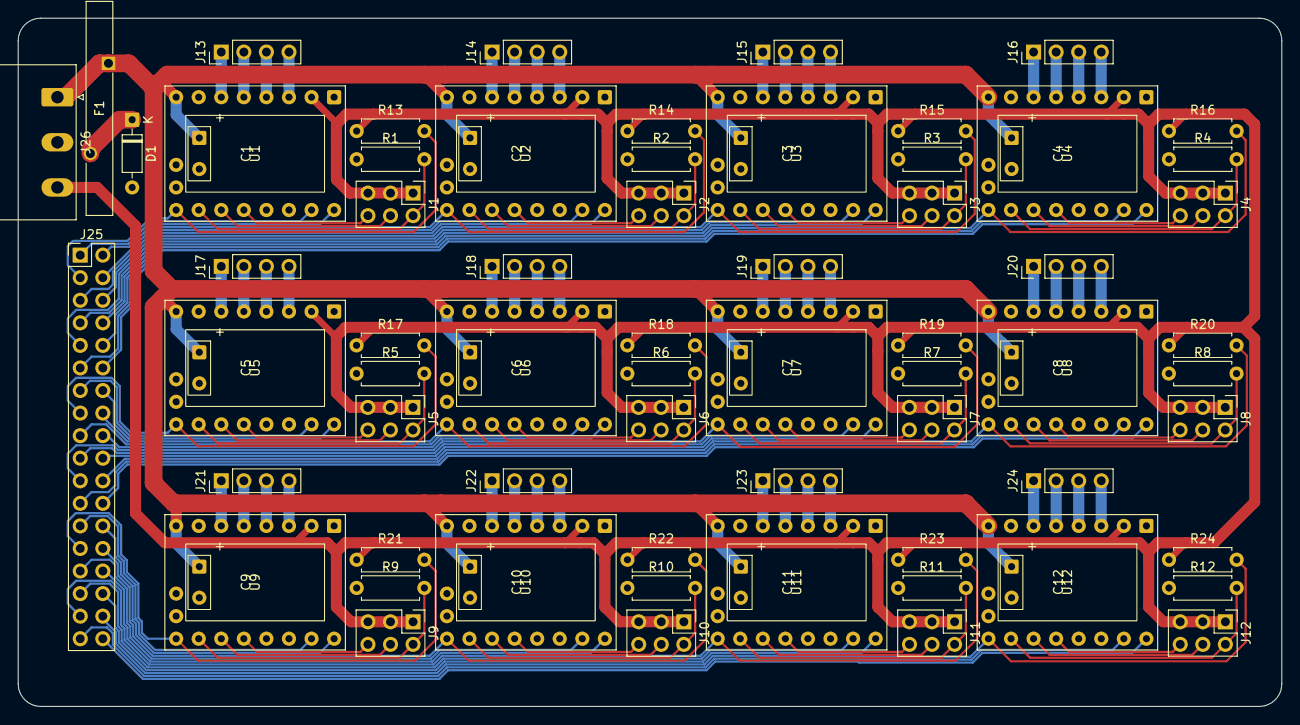
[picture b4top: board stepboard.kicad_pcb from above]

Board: 2 copper layers, 142.2 x 77.5 mm, 76 parts (0 on the bottom side), 124 nets.
